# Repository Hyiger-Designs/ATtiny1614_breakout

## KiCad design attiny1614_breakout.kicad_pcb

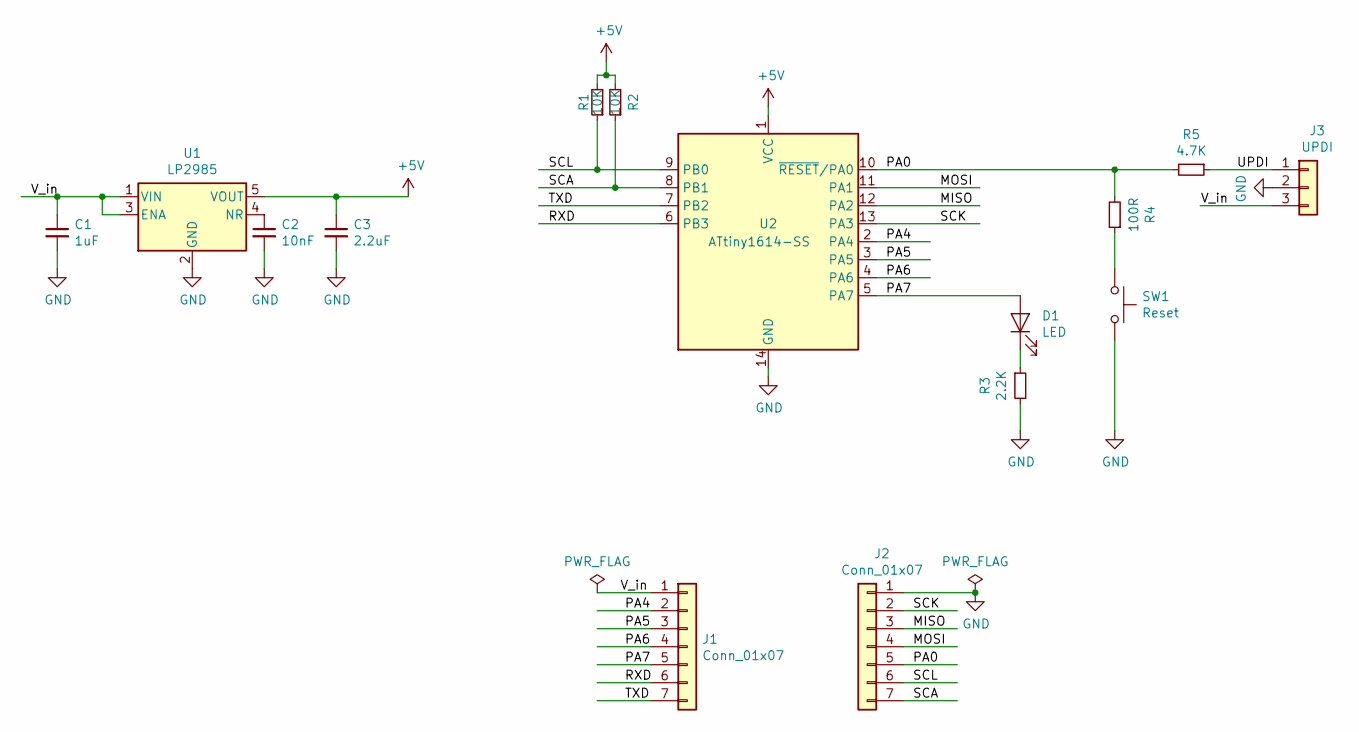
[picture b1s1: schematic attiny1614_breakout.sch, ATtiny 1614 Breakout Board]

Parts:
C1: 1uF; C_0603_1608Metric_Pad1.05x0.95mm_HandSolder
C2: 10nF; C_0603_1608Metric_Pad1.05x0.95mm_HandSolder
C3: 2.2uF; C_0603_1608Metric_Pad1.05x0.95mm_HandSolder
D1: LED; LED_0603_1608Metric_Pad1.05x0.95mm_HandSolder
J1, J2: Conn_01x07; PinHeader_1x07_P2.54mm_Vertical
J3: UPDI; PinHeader_1x03_P2.54mm_Vertical
R1, R2: 10K; R_0603_1608Metric_Pad1.05x0.95mm_HandSolder
R3: 2.2K; R_0603_1608Metric_Pad1.05x0.95mm_HandSolder
R4: 100R; R_0603_1608Metric_Pad1.05x0.95mm_HandSolder
R5: 4.7K; R_0603_1608Metric_Pad1.05x0.95mm_HandSolder
SW1: Reset; SW_Push_SPST_NO_Alps_SKRK
U1: LP2985; SOT-23-5
U2: ATtiny1614-SS; SOIC-14_3.9x8.7mm_P1.27mm

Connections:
+5V: C3.1, R1.2, R2.2, U1.5 (VOUT), U2.1 (VCC)
/MISO: J2.3, U2.12 (PA2)
/MOSI: J2.4, U2.11 (PA1)
/PA0: J2.5, R4.2, R5.2, U2.10 (~RESET~/PA0)
/PA4: J1.2, U2.2 (PA4)
/PA5: J1.3, U2.3 (PA5)
/PA6: J1.4, U2.4 (PA6)
/PA7: D1.2 (A), J1.5, U2.5 (PA7)
/RXD: J1.6, U2.6 (PB3)
/SCA: J2.7, R2.1, U2.8 (PB1)
/SCK: J2.2, U2.13 (PA3)
/SCL: J2.6, R1.1, U2.9 (PB0)
/TXD: J1.7, U2.7 (PB2)
/UPDI: J3.1, R5.1
/V_in: C1.1, J1.1, J3.3, U1.1 (VIN), U1.3 (ENA)
GND: C1.2, C2.2, C3.2, J2.1, J3.2, R3.2, SW1.2, U1.2 (GND), U2.14 (GND)
unnamed: C2.1, U1.4 (NR)
unnamed: D1.1 (K), R3.1
unnamed: R4.1, SW1.1

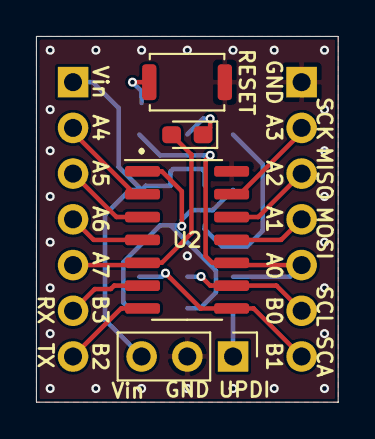
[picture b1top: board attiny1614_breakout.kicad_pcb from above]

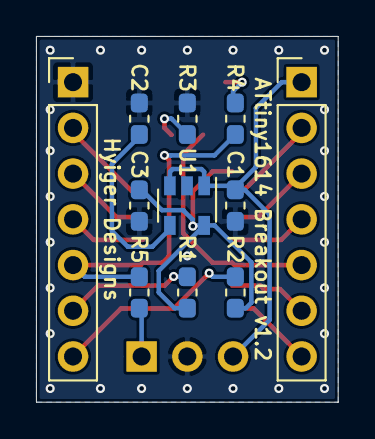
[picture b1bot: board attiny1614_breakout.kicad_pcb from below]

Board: 2 copper layers, 16.8 x 20.3 mm, 15 parts (11 on the bottom side), 19 nets.

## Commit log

2019-09-08 Initial version 1.0
2019-09-08 fixed solder mask clearance
2019-09-23 moved to programmer pin to Vin, fixed typos, added thermal relief
2019-09-23 Fixed silkscreen typos
2019-09-24 additional silkscreen labels, cleaned-up gnd plane
2019-09-24 simplified power section
2019-09-25 changed VCC to 5V
2020-02-04 version upgrade
